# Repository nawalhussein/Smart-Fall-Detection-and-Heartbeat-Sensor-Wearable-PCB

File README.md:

# ATmega32 Smart Watch & Fall Detection System

This repository contains the hardware schematics, PCB design, and bare-metal firmware for a wearable Smart Watch featuring real-time health monitoring and automated fall detection.

### Brief Project Description

This wearable device is designed to monitor user vitals and detect sudden falls, transmitting emergency data wirelessly. The system leverages an 8-bit AVR architecture optimized for low power consumption.

Key components and subsystems include:
* **Microcontroller:** An ATmega32A MCU managing sensor data acquisition, threshold calculations, and peripheral communication.
* **Inertial Measurement (Fall Detection):** An **MPU6050** 6-axis gyroscope/accelerometer connected via **I2C**. It continuously samples acceleration forces to detect sudden impacts or unusual orientation changes indicative of a fall.
* **Health Monitoring:** A **MAX30102** pulse oximeter and heart-rate sensor (also on the **I2C** bus) tracks biometric data.
* **Wireless Connectivity:** An **ESP-01 (ESP8266)** Wi-Fi module interfaces via **UART** to upload telemetry data to a cloud server or trigger remote alerts.
* **User Interface:** Features a localized notification system using a hardware buzzer, status LEDs (Green, Yellow, Red), and manual push buttons for user interaction (e.g., canceling a false alarm).
* **Power Management Network:** Designed for portability, the system runs on a **3.7V Li-ion battery** with an integrated charging module, a **Boost Converter** to step up voltage, and dedicated **5V and 3.3V regulators** to cleanly power the mixed-voltage rails.
* **In-System Programming:** Features a dedicated **USBASP** hardware header for direct ISP flashing and debugging.

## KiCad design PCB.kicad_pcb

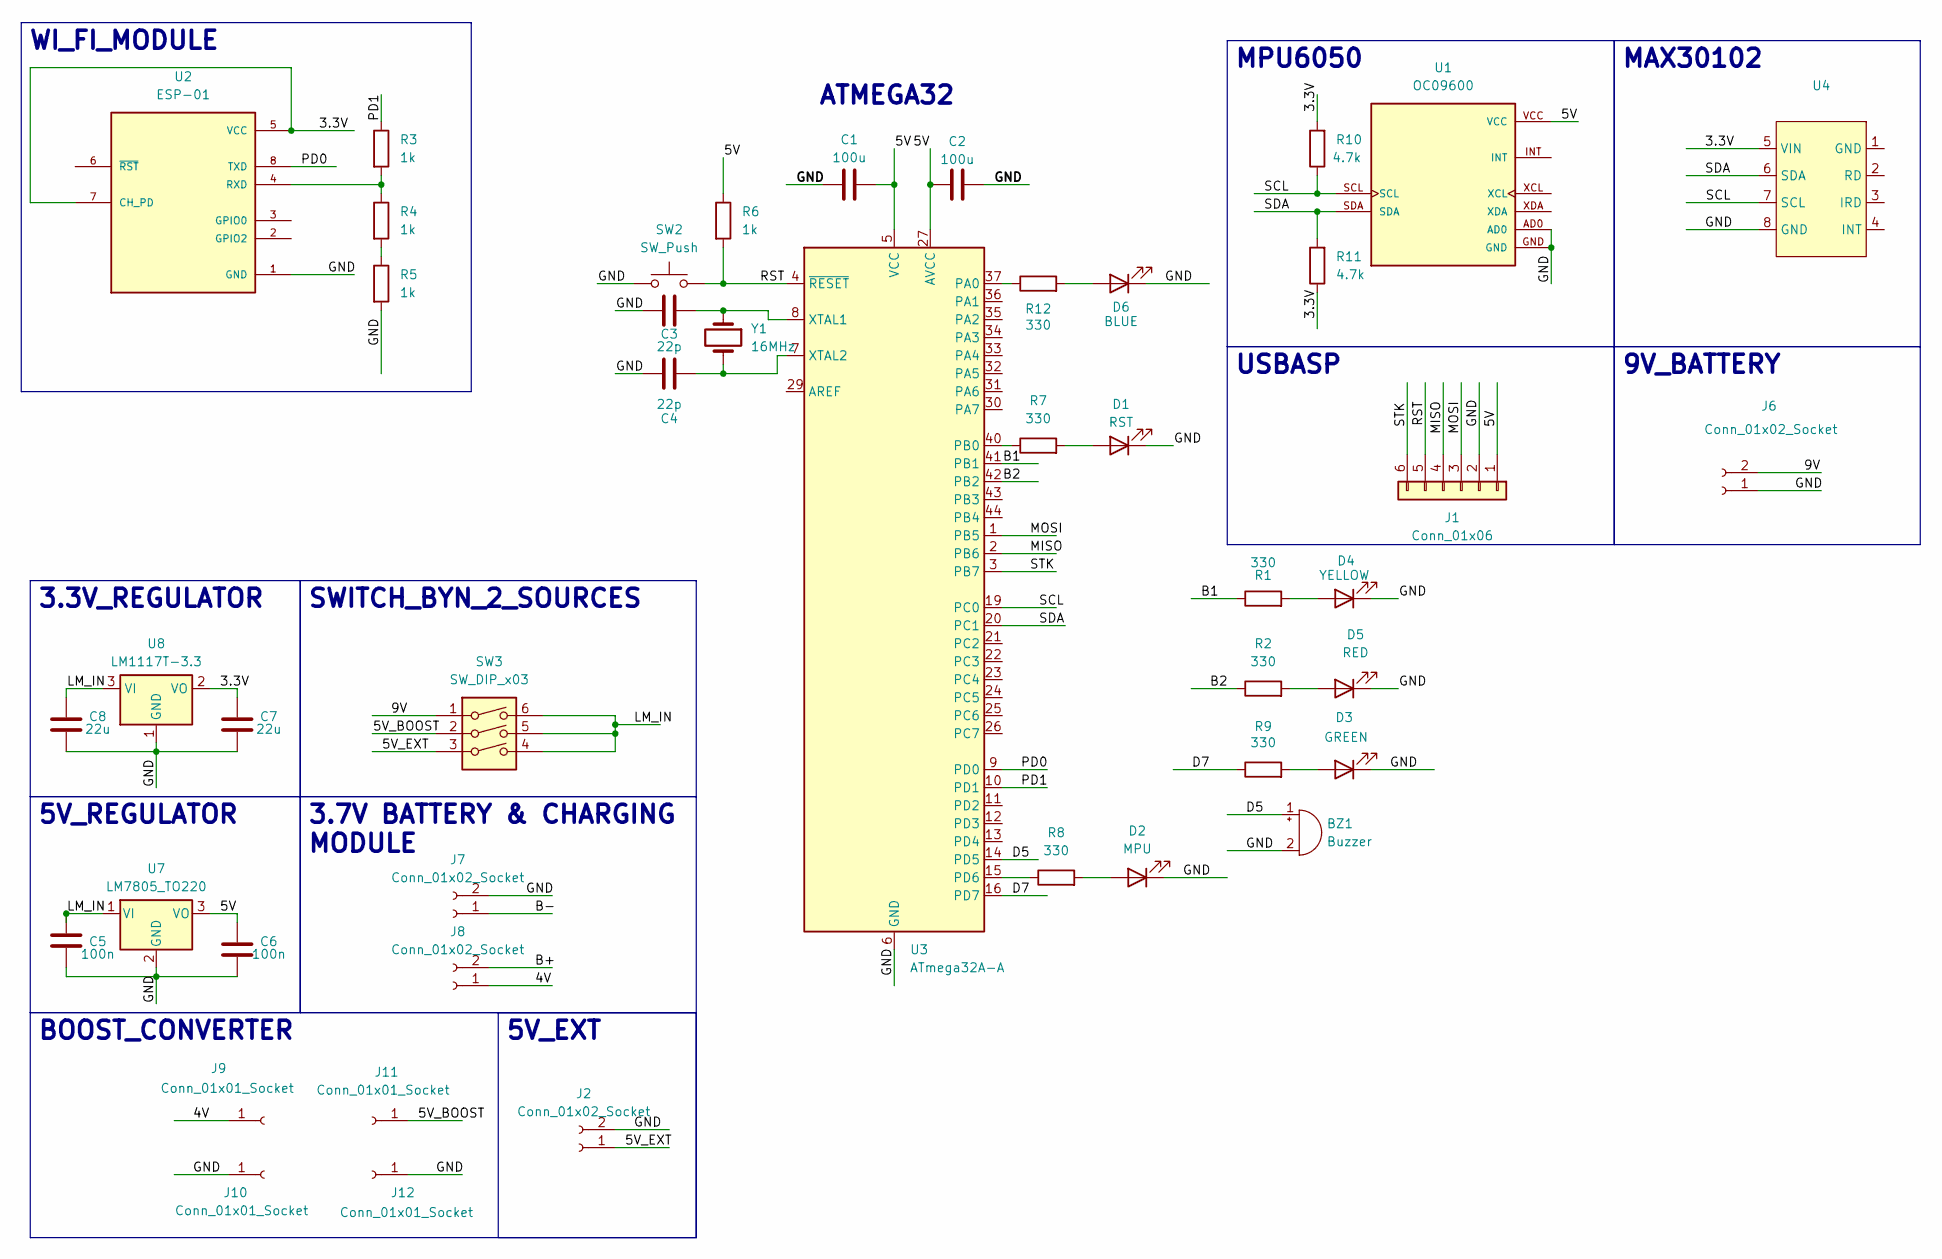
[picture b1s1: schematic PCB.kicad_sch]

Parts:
BZ1: Buzzer; Buzzer_12x9.5RM7.6
C1, C2: 100u; C_1206_3216Metric
C3, C4: 22p; C_1206_3216Metric
C5, C6: 100n; C_0603_1608Metric
C7, C8: 22u; C_0805_2012Metric
D1: RST; LED_1206_3216Metric
D2: MPU; LED_1206_3216Metric
D3: GREEN; LED_1206_3216Metric
D4: YELLOW; LED_1206_3216Metric
D5: RED; LED_1206_3216Metric
D6: BLUE; LED_1206_3216Metric
J1: Conn_01x06; PinSocket_1x06_P2.54mm_Vertical
J2, J6, J7, J8: Conn_01x02_Socket; PinSocket_1x02_P2.54mm_Vertical
J9, J10, J11, J12: Conn_01x01_Socket; PinSocket_1x01_P2.54mm_Vertical
R1, R2, R7, R8, R9, R12: 330; R_0603_1608Metric
R3, R4, R5, R6: 1k; R_0603_1608Metric
R10, R11: 4.7k; R_0603_1608Metric
SW2: SW_Push; SW_PUSH_6mm_2pin_custom
SW3: SW_DIP_x03; SW_DIP_SPSTx03_Slide_9.78x9.8mm_W7.62mm_P2.54mm
U1: OC09600; MODULE_OC09600; PARTREV NA
U2: ESP-01; MODULE_ESP-01; PARTREV 1.0
U3: ATmega32A-A; TQFP-44_10x10mm_P0.8mm
U4: MAX30102
U7: LM7805_TO220; TO-220-3_Vertical
U8: LM1117T-3.3; TO-220-3_Vertical
Y1: 16MHz; Crystal_HC49-4H_Vertical

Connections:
/3.3V: C7.2, R10.2, R11.1, U2.5 (VCC), U2.7 (CH_PD), U4.5 (VIN), U8.2 (VO)
/4V: J8.1, J9.1
/5V: C1.2, C2.1, C6.2, J1.1, R6.1, U1.VCC, U3.5 (VCC), U3.17 (VCC), U3.27 (AVCC), U3.38 (VCC), U7.3 (VO)
/5V_BOOST: J11.1, SW3.2
/5V_EXT: J2.1, SW3.3
/9V: J6.2, SW3.1
/B1: R1.1, U3.41 (PB1)
/B2: R2.1, U3.42 (PB2)
/B+: J8.2
/B-: J7.1
/D5: BZ1.1 (+), U3.14 (PD5)
/D7: R9.1, U3.16 (PD7)
/GND: BZ1.2 (-), C1.1, C2.2, C3.1, C4.1, C5.1, C6.1, C7.1, C8.1, D1.1 (K), D2.1 (K), D3.1 (K), D4.1 (K), D5.1 (K), D6.1 (K), J1.2, J2.2, J6.1, J7.2, J10.1, J12.1, R5.2, SW2.1, U1.AD0, U1.GND, U2.1 (GND), U3.6 (GND), U3.28 (GND), U3.39 (GND), U4.8 (GND), U7.2 (GND), U8.1 (GND)
/LM_IN: C5.2, C8.2, SW3.4, SW3.5, SW3.6, U7.1 (VI), U8.3 (VI)
/MISO: J1.4, U3.2 (PB6)
/MOSI: J1.3, U3.1 (PB5)
/PD0: U2.8 (TXD), U3.9 (PD0)
/PD1: R3.1, U3.10 (PD1)
/RST: J1.5, R6.2, SW2.2, U3.4 (~RESET)
/SCL: R10.1, U1.SCL, U3.19 (PC0), U4.7 (SCL)
/SDA: R11.2, U1.SDA, U3.20 (PC1), U4.6 (SDA)
/STK: J1.6, U3.3 (PB7)
unnamed: D1.2 (A), R7.2
unnamed: D2.2 (A), R8.2
unnamed: D3.2 (A), R9.2
unnamed: D4.2 (A), R1.2
unnamed: D5.2 (A), R2.2
unnamed: D6.2 (A), R12.2
unnamed: R4.2, R5.1
unnamed: R3.2, R4.1, U2.4 (RXD)
unnamed: R12.1, U3.37 (PA0)
unnamed: R7.1, U3.40 (PB0)
unnamed: R8.1, U3.15 (PD6)
unnamed: C3.2, U3.8 (XTAL1), Y1.1
unnamed: C4.2, U3.7 (XTAL2), Y1.2

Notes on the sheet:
ATMEGA32
MAX30102
9V_BATTERY
USBASP
MPU6050
3.3V_REGULATOR
5V_EXT
3.7V BATTERY & CHARGING MODULE
BOOST_CONVERTER
WI_FI_MODULE
5V_REGULATOR
SWITCH_BYN_2_SOURCES

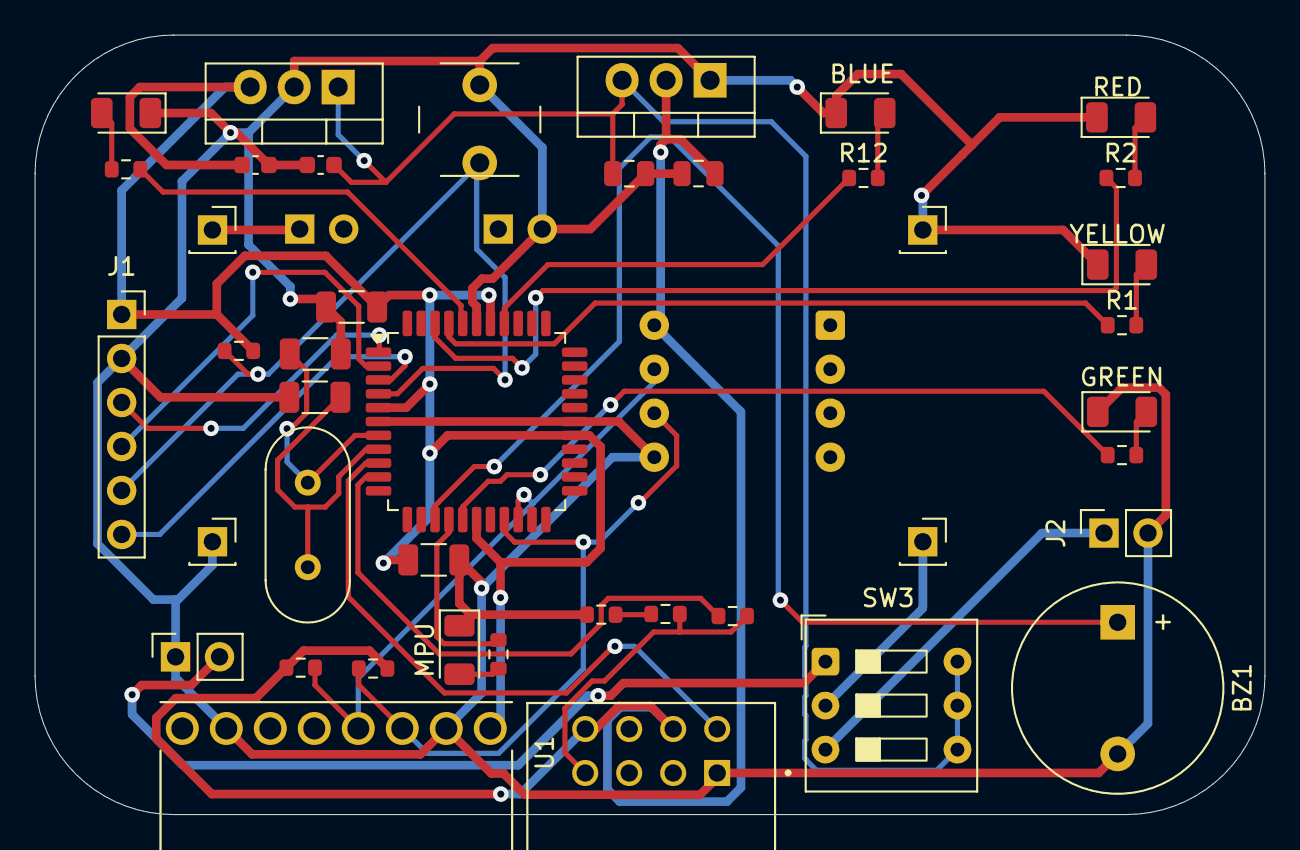
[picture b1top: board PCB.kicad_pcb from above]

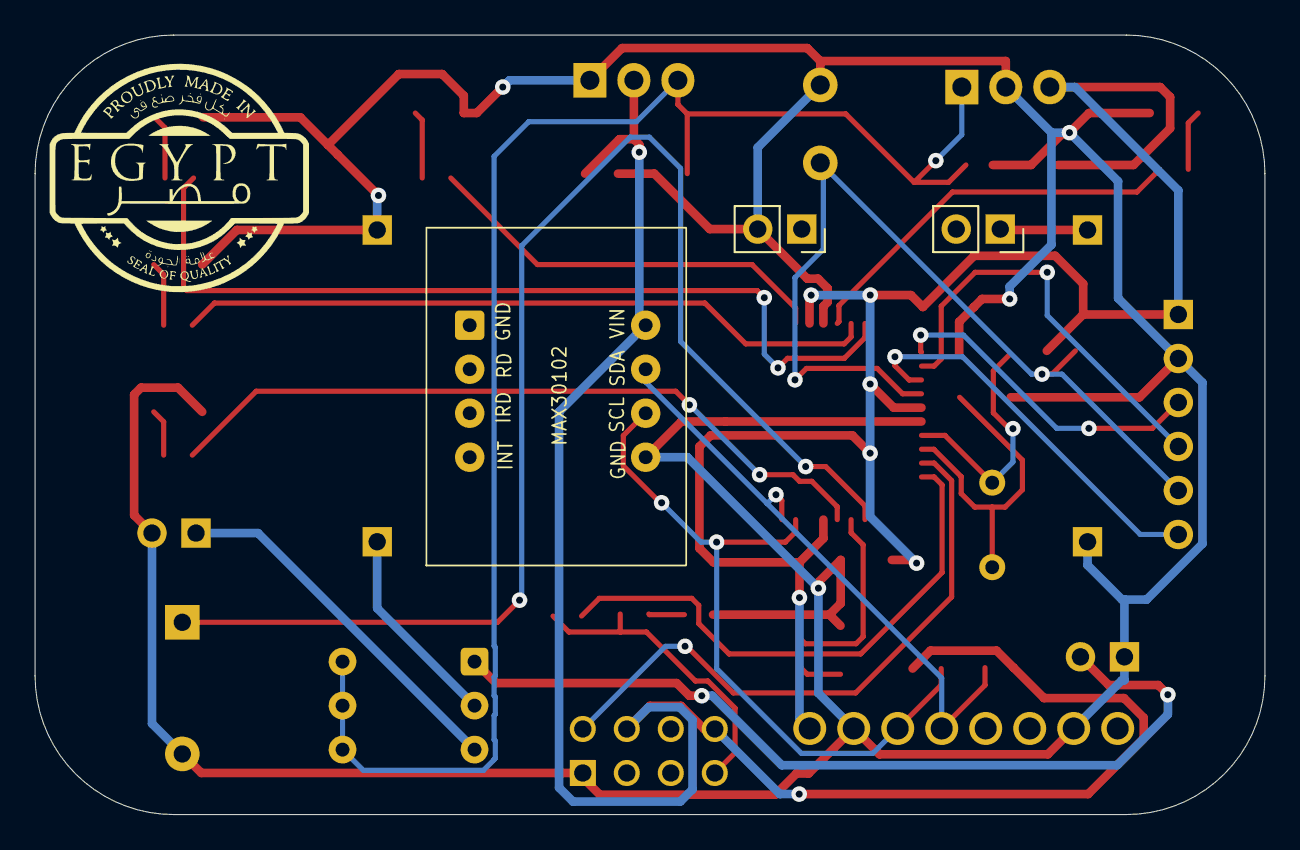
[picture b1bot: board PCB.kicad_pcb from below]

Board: 2 copper layers, 71.0 x 45.0 mm, 45 parts (3 on the bottom side), 33 nets.

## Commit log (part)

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2026-06-22 Added KiCad Files
